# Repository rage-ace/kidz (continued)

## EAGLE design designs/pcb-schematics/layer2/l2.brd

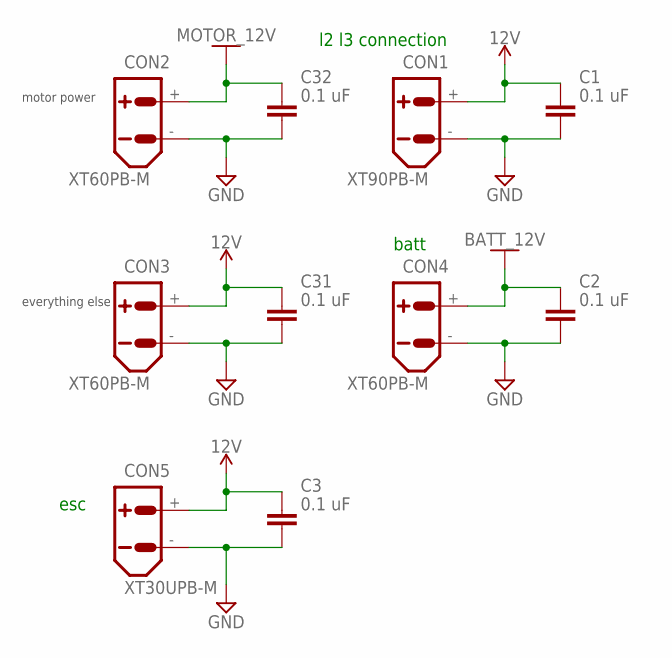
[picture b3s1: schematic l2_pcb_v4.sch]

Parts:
C1, C2, C3, C31, C32: 0.1 uF; CAPC1608X85
CON1: XT90PB-M
CON2, CON3, CON4: XT60PB-M
CON5: XT30UPB-M

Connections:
12V: C1.1, C3.1, C31.1, CON1.+, CON3.+, CON5.+
BATT_12V: C2.1, CON4.+
GND: C1.2, C2.2, C3.2, C31.2, C32.2, CON1.-, CON2.-, CON3.-, CON4.-, CON5.-
MOTOR_12V: C32.1, CON2.+

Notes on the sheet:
motor power
everything else
l2 l3 connection
batt
esc

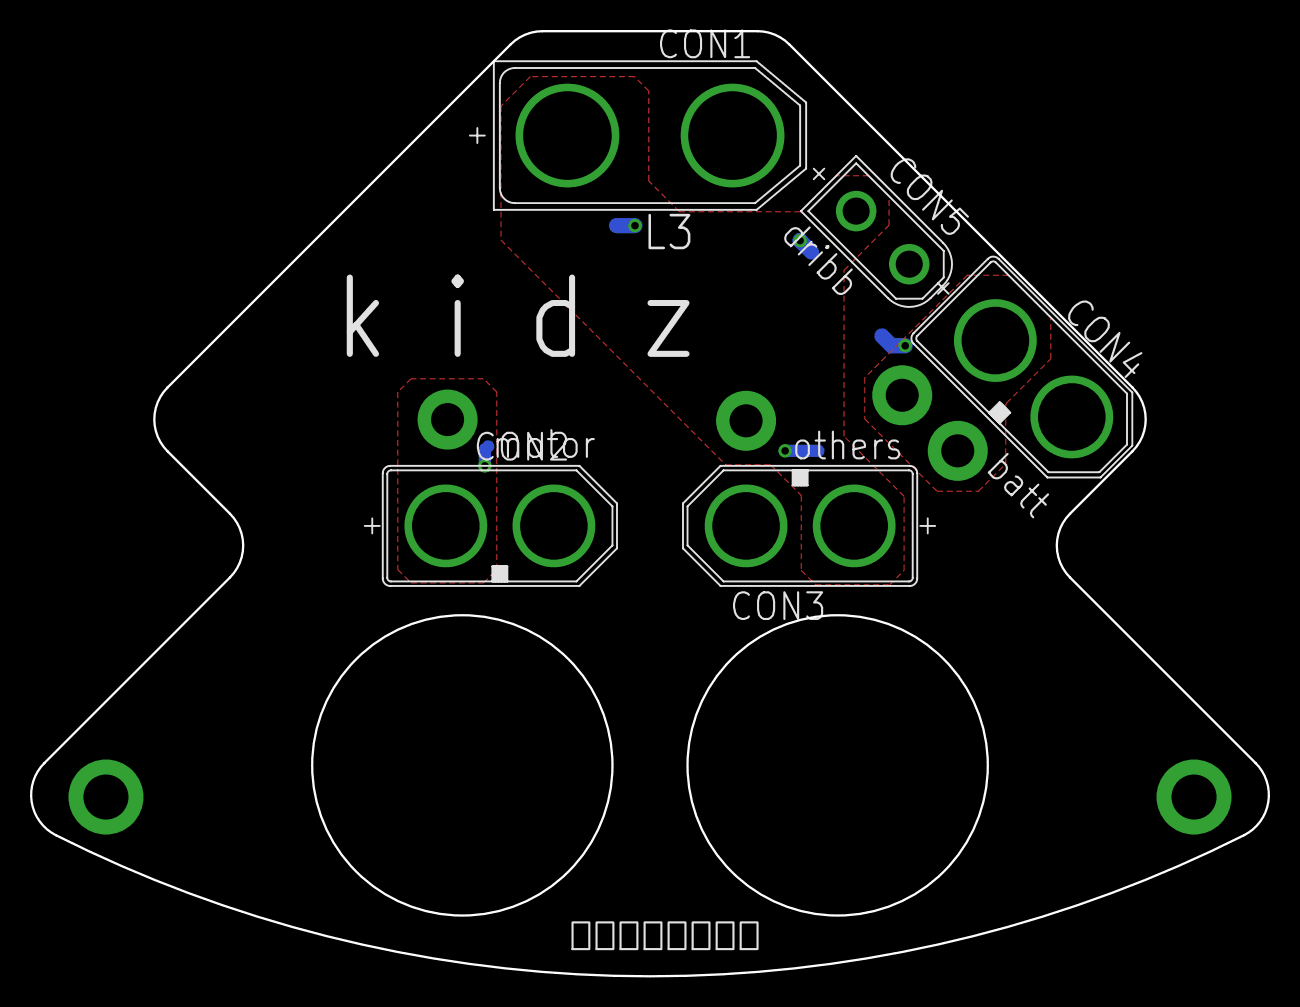
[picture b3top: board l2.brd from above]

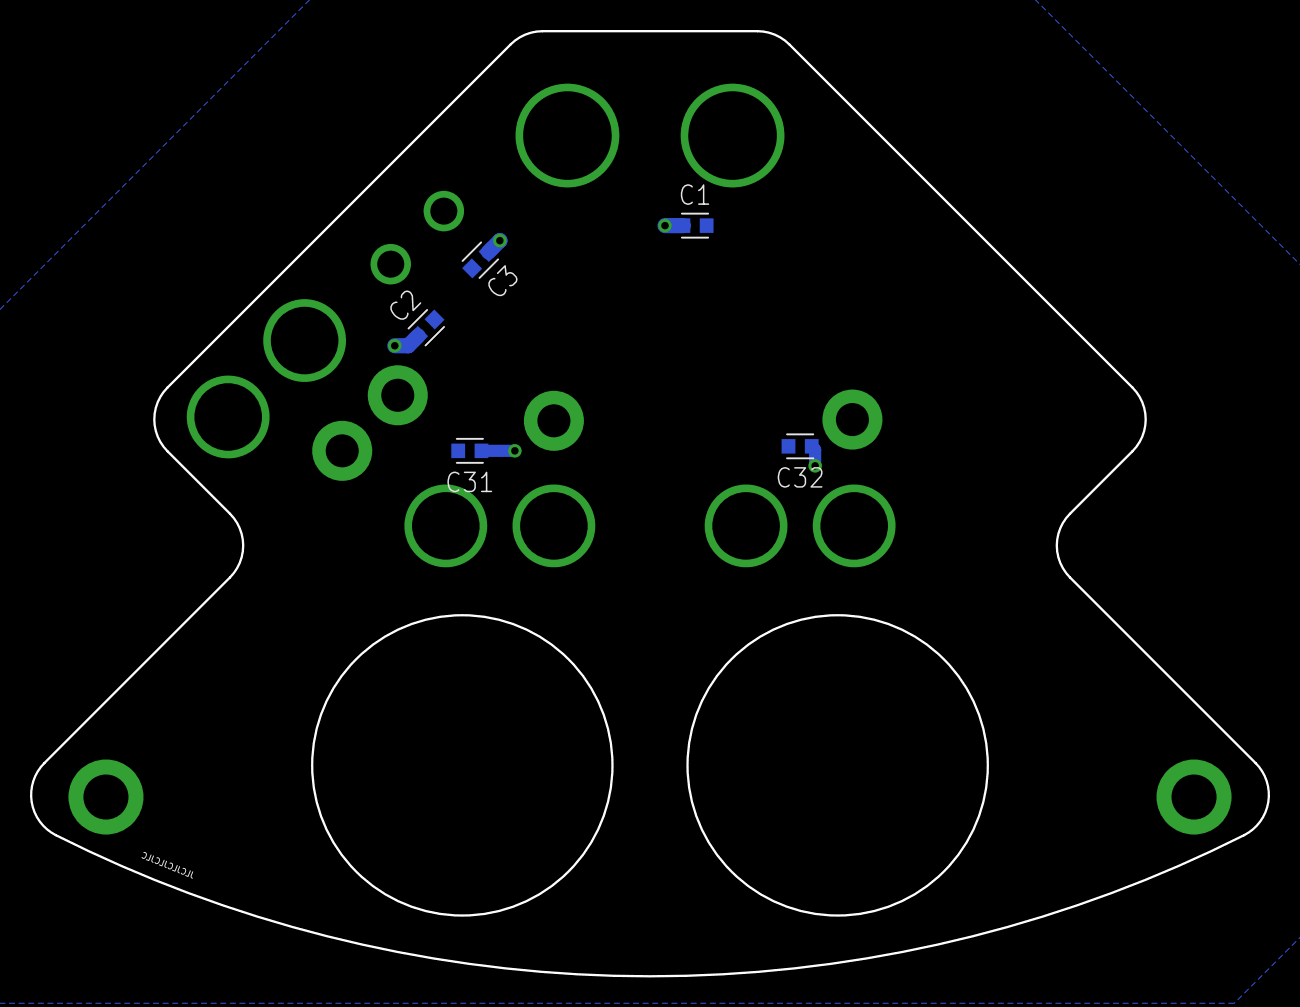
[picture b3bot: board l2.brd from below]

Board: 2 copper layers, 82.4 x 63.0 mm, 10 parts (5 on the bottom side), 4 nets.

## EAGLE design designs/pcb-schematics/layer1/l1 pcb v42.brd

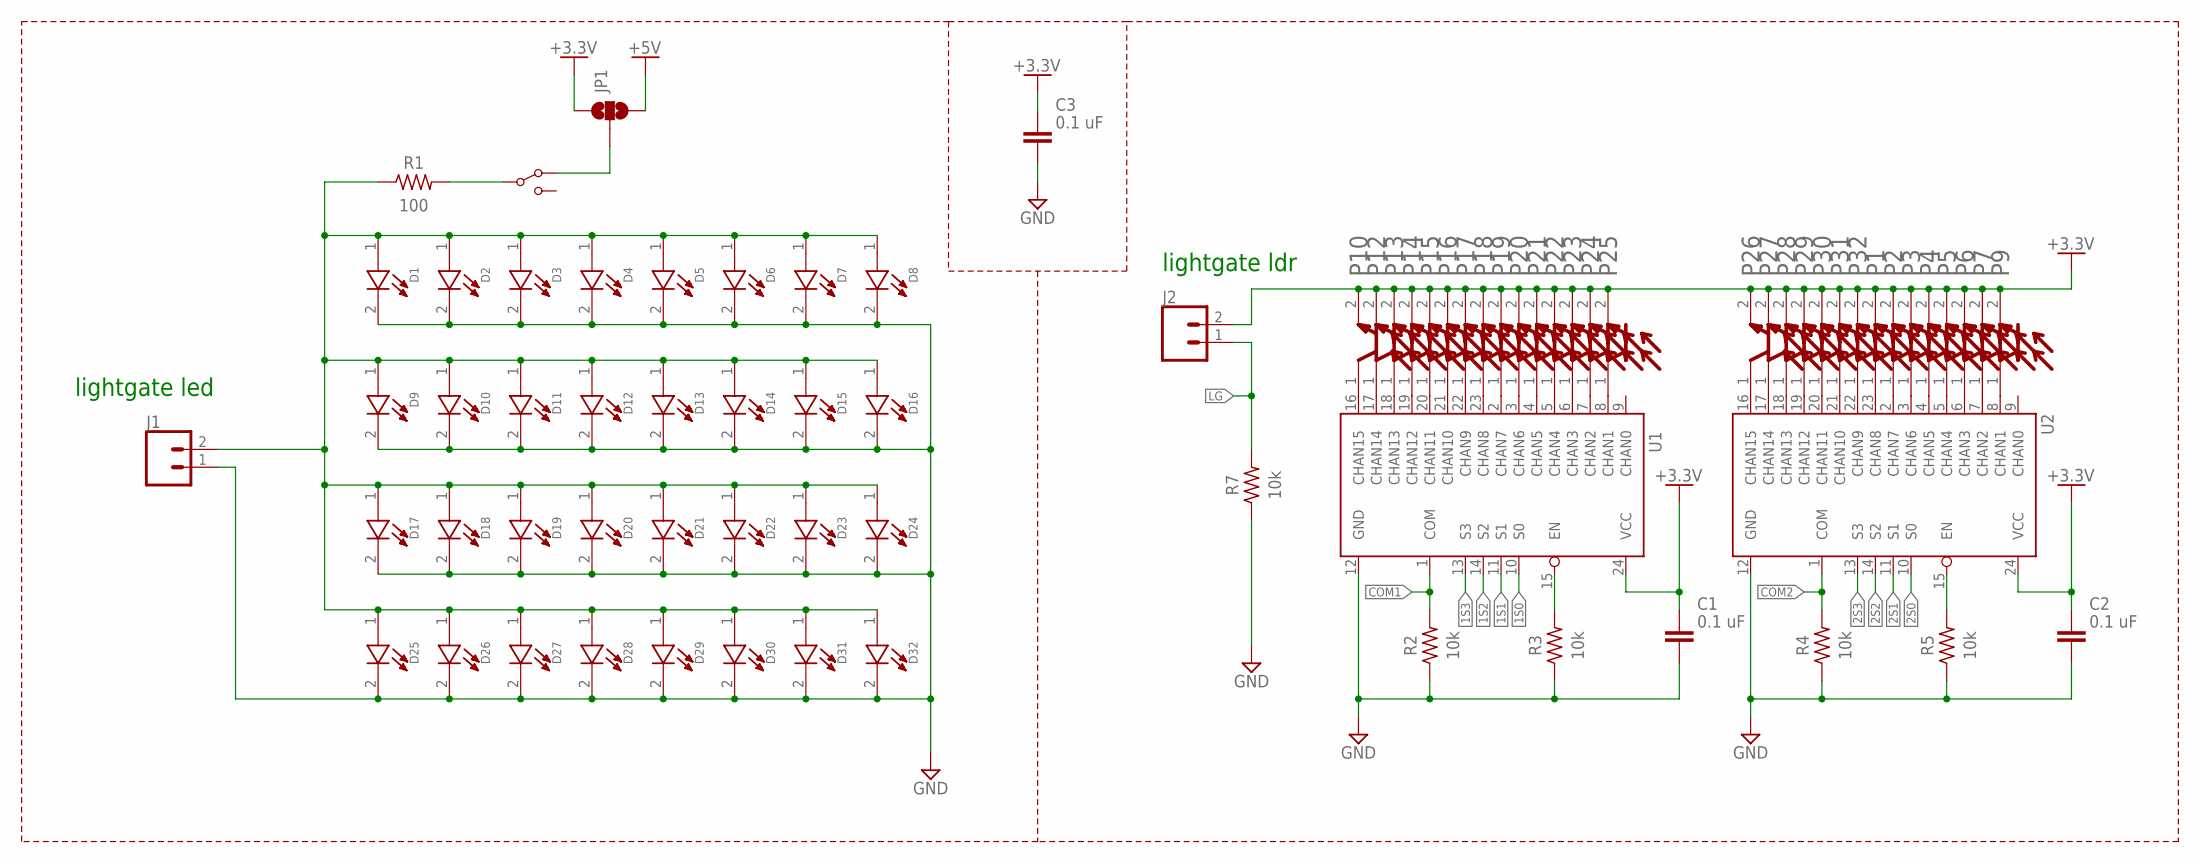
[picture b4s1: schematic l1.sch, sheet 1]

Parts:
C1, C2, C3: 0.1 uF; CAPC1608X85
D1, D2, D3, D4, D5, D6, D7, D8, D9, D10, D11, D12, D13, D14, D15, D16, D17, D18, D19, D20, D21, D22, D23, D24, D25, D26, D27, D28, D29, D30, D31, D32: OF-SMD3528WCLED; LED
J1, J2: CONN_02; 1X02
JP1: JUMPER-SMT_3_NO_SILK; SMT-JUMPER_3_NO_SILK
P1, P2, P3, P4, P5, P6, P7, P9, P10, P12, P13, P14, P15, P16, P17, P18, P19, P20, P21, P22, P23, P24, P25, P26, P27, P28, P29, P30, P31, P32: EVERLIGHT_ALS-PT19-315C-L177-TR8; ALS-PT19
R1: 100; RESC1608X60
R2, R3, R4, R5, R7: 10k; RESC1608X60
S1: SPDT-SLIDE-SWITCHSWITCH-TH; SWITCH-TH
U1, U2: 74HC4067SM96; SSOP24

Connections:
1S0: U1.10 (S0); also elsewhere on the board
1S1: U1.11 (S1); also elsewhere on the board
1S2: U1.14 (S2); also elsewhere on the board
1S3: U1.13 (S3); also elsewhere on the board
2S0: U2.10 (S0); also elsewhere on the board
2S1: U2.11 (S1); also elsewhere on the board
2S2: U2.14 (S2); also elsewhere on the board
2S3: U2.13 (S3); also elsewhere on the board
+3.3V: C1.1, C2.1, C3.1, J2.2, JP1.1, P1.2 (EMITTER), P2.2 (EMITTER), P3.2 (EMITTER), P4.2 (EMITTER), P5.2 (EMITTER), P6.2 (EMITTER), P7.2 (EMITTER), P9.2 (EMITTER), P10.2 (EMITTER), P12.2 (EMITTER), P13.2 (EMITTER), P14.2 (EMITTER), P15.2 (EMITTER), P16.2 (EMITTER), P17.2 (EMITTER), P18.2 (EMITTER), P19.2 (EMITTER), P20.2 (EMITTER), P21.2 (EMITTER), P22.2 (EMITTER), P23.2 (EMITTER), P24.2 (EMITTER), P25.2 (EMITTER), P26.2 (EMITTER), P27.2 (EMITTER), P28.2 (EMITTER), P29.2 (EMITTER), P30.2 (EMITTER), P31.2 (EMITTER), P32.2 (EMITTER), U1.24 (VCC), U2.24 (VCC); also elsewhere on the board
+5V: JP1.3; also elsewhere on the board
COM1: R2.2, U1.1 (COM); also elsewhere on the board
COM2: R4.2, U2.1 (COM); also elsewhere on the board
GND: C1.2, C2.2, C3.2, D1.2 (C), D2.2 (C), D3.2 (C), D4.2 (C), D5.2 (C), D6.2 (C), D7.2 (C), D8.2 (C), D9.2 (C), D10.2 (C), D11.2 (C), D12.2 (C), D13.2 (C), D14.2 (C), D15.2 (C), D16.2 (C), D17.2 (C), D18.2 (C), D19.2 (C), D20.2 (C), D21.2 (C), D22.2 (C), D23.2 (C), D24.2 (C), D25.2 (C), D26.2 (C), D27.2 (C), D28.2 (C), D29.2 (C), D30.2 (C), D31.2 (C), D32.2 (C), J1.1, R2.1, R3.1, R4.1, R5.1, R7.1, U1.12 (GND), U2.12 (GND); also elsewhere on the board
LG: J2.1, R7.2; also elsewhere on the board
unnamed: JP1.2, S1.P$1
unnamed: R3.2, U1.15 (EN)
unnamed: D1.1 (A), D2.1 (A), D3.1 (A), D4.1 (A), D5.1 (A), D6.1 (A), D7.1 (A), D8.1 (A), D9.1 (A), D10.1 (A), D11.1 (A), D12.1 (A), D13.1 (A), D14.1 (A), D15.1 (A), D16.1 (A), D17.1 (A), D18.1 (A), D19.1 (A), D20.1 (A), D21.1 (A), D22.1 (A), D23.1 (A), D24.1 (A), D25.1 (A), D26.1 (A), D27.1 (A), D28.1 (A), D29.1 (A), D30.1 (A), D31.1 (A), D32.1 (A), J1.2, R1.1
unnamed: R5.2, U2.15 (EN)
unnamed: R1.2, S1.P$2
unnamed: P25.1 (COLLECTOR), U1.8 (CHAN1)
unnamed: P17.1 (COLLECTOR), U1.22 (CHAN9)
unnamed: P18.1 (COLLECTOR), U1.23 (CHAN8)
unnamed: P19.1 (COLLECTOR), U1.2 (CHAN7)
unnamed: P20.1 (COLLECTOR), U1.3 (CHAN6)
unnamed: P21.1 (COLLECTOR), U1.4 (CHAN5)
unnamed: P22.1 (COLLECTOR), U1.5 (CHAN4)
unnamed: P23.1 (COLLECTOR), U1.6 (CHAN3)
unnamed: P24.1 (COLLECTOR), U1.7 (CHAN2)
unnamed: P10.1 (COLLECTOR), U1.16 (CHAN15)
unnamed: P12.1 (COLLECTOR), U1.17 (CHAN14)
unnamed: P13.1 (COLLECTOR), U1.18 (CHAN13)
unnamed: P14.1 (COLLECTOR), U1.19 (CHAN12)
unnamed: P15.1 (COLLECTOR), U1.20 (CHAN11)
unnamed: P16.1 (COLLECTOR), U1.21 (CHAN10)
unnamed: P9.1 (COLLECTOR), U2.8 (CHAN1)
unnamed: P1.1 (COLLECTOR), U2.23 (CHAN8)
unnamed: P2.1 (COLLECTOR), U2.2 (CHAN7)
unnamed: P3.1 (COLLECTOR), U2.3 (CHAN6)
unnamed: P4.1 (COLLECTOR), U2.4 (CHAN5)
unnamed: P5.1 (COLLECTOR), U2.5 (CHAN4)
unnamed: P6.1 (COLLECTOR), U2.6 (CHAN3)
unnamed: P7.1 (COLLECTOR), U2.7 (CHAN2)
unnamed: P26.1 (COLLECTOR), U2.16 (CHAN15)
unnamed: P27.1 (COLLECTOR), U2.17 (CHAN14)
unnamed: P28.1 (COLLECTOR), U2.18 (CHAN13)
unnamed: P29.1 (COLLECTOR), U2.19 (CHAN12)
unnamed: P30.1 (COLLECTOR), U2.20 (CHAN11)
unnamed: P31.1 (COLLECTOR), U2.21 (CHAN10)
unnamed: P32.1 (COLLECTOR), U2.22 (CHAN9)

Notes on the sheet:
lightgate led
lightgate ldr

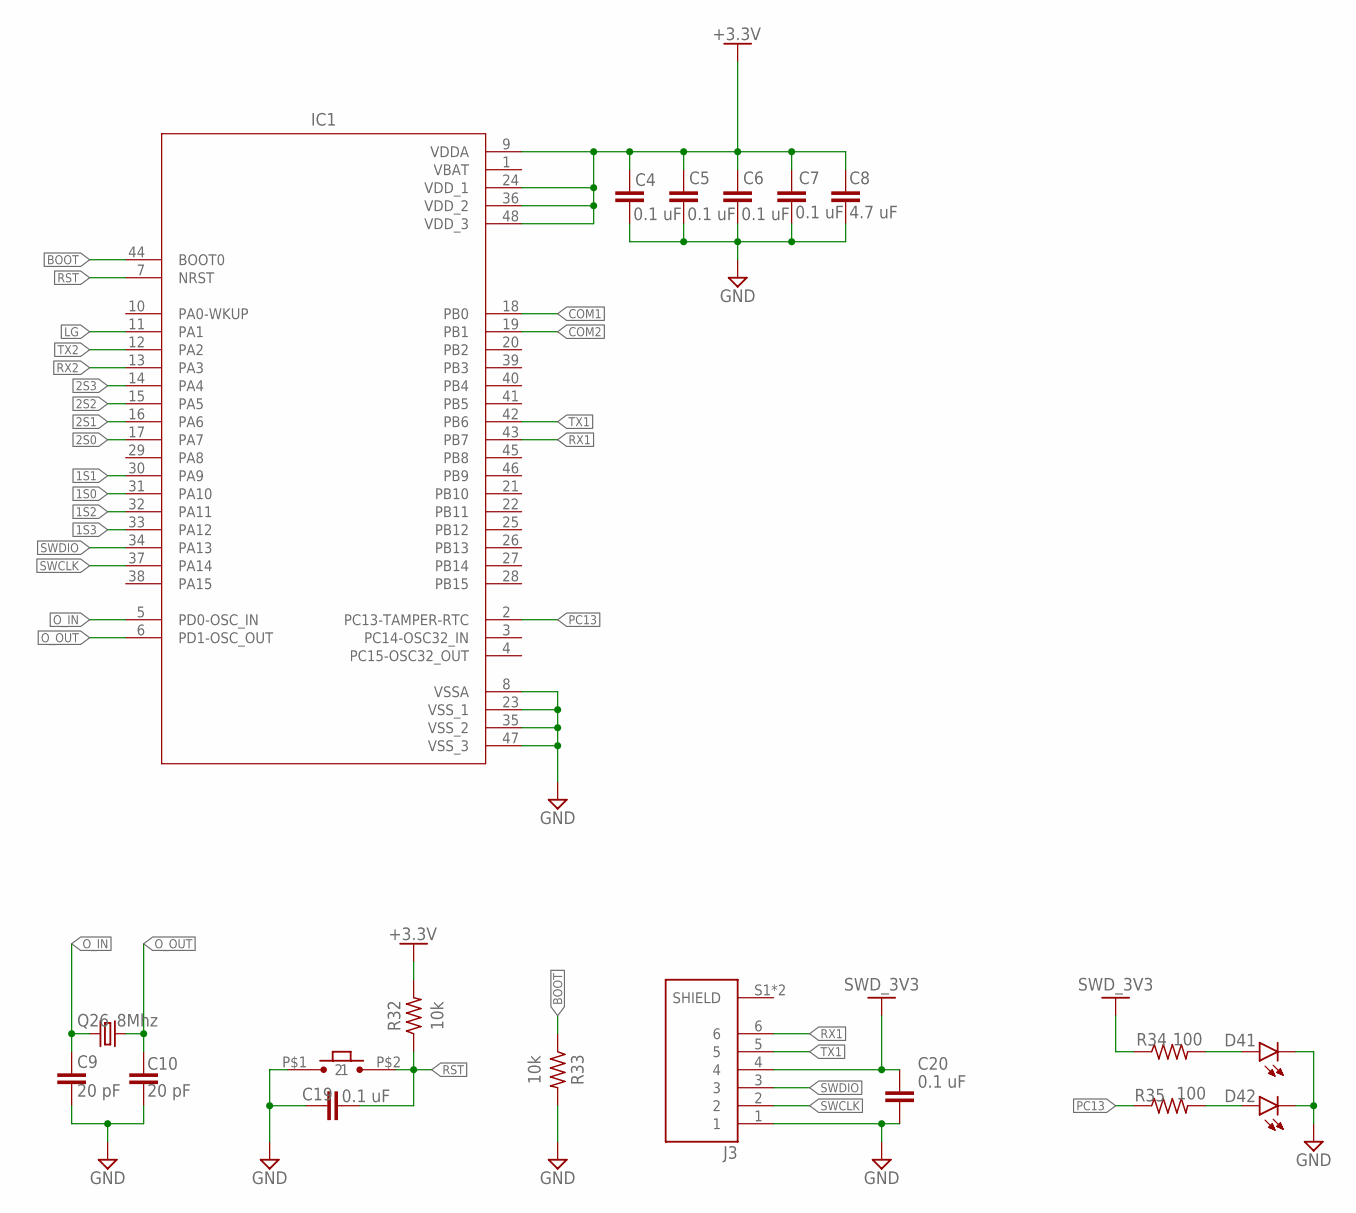
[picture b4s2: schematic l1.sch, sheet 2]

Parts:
C4, C5, C6, C7, C19, C20: 0.1 uF; CAPC1608X85
C8: 4.7 uF; CAPC1608X85
C9, C10: 20 pF; CAPC1608X85
D41, D42: CHIP-FLAT-G_0603-0.35MM; LEDC1608X35N_FLAT-G
IC1: STM32F103_QFP; QFP50P900X900X160-48N
J3: SM06B-SRSS-TB(LF)(SN); JST_SM06B-SRSS-TB(LF)(SN)
Q26: 8Mhz; CTS406
R32, R33: 10k; RESC1608X60
R34, R35: 100; RESC1608X60
U$1: SMOL_TACTILE_3X4MM

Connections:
1S0: IC1.31 (PA10); also elsewhere on the board
1S1: IC1.30 (PA9); also elsewhere on the board
1S2: IC1.32 (PA11); also elsewhere on the board
1S3: IC1.33 (PA12); also elsewhere on the board
2S0: IC1.17 (PA7); also elsewhere on the board
2S1: IC1.16 (PA6); also elsewhere on the board
2S2: IC1.15 (PA5); also elsewhere on the board
2S3: IC1.14 (PA4); also elsewhere on the board
+3.3V: C4.1, C5.1, C6.1, C7.1, C8.1, IC1.9 (VDDA), IC1.24 (VDD_1), IC1.36 (VDD_2), IC1.48 (VDD_3), R32.2; also elsewhere on the board
BOOT: IC1.44 (BOOT0), R33.1
COM1: IC1.18 (PB0); also elsewhere on the board
COM2: IC1.19 (PB1); also elsewhere on the board
GND: C4.2, C5.2, C6.2, C7.2, C8.2, C9.2, C10.2, C19.1, C20.2, D41.C, D42.C, IC1.8 (VSSA), IC1.23 (VSS_1), IC1.35 (VSS_2), IC1.47 (VSS_3), J3.1, R33.2, U$1.P$1 (1); also elsewhere on the board
LG: IC1.11 (PA1); also elsewhere on the board
unnamed: D41.A, R34.2
unnamed: D42.A, R35.2
O_IN: C9.1, IC1.5 (PD0-OSC_IN), Q26.1
O_OUT: C10.1, IC1.6 (PD1-OSC_OUT), Q26.3 (2)
PC13: IC1.2 (PC13-TAMPER-RTC), R35.1
RST: C19.2, IC1.7 (NRST), R32.1, U$1.P$2 (2)
RX1: IC1.43 (PB7), J3.6
RX2: IC1.13 (PA3); also elsewhere on the board
SWCLK: IC1.37 (PA14), J3.2
SWDIO: IC1.34 (PA13), J3.3
SWD_3V3: C20.1, J3.4, R34.1
TX1: IC1.42 (PB6), J3.5
TX2: IC1.12 (PA2); also elsewhere on the board
VBAT: IC1.1 (VBAT)

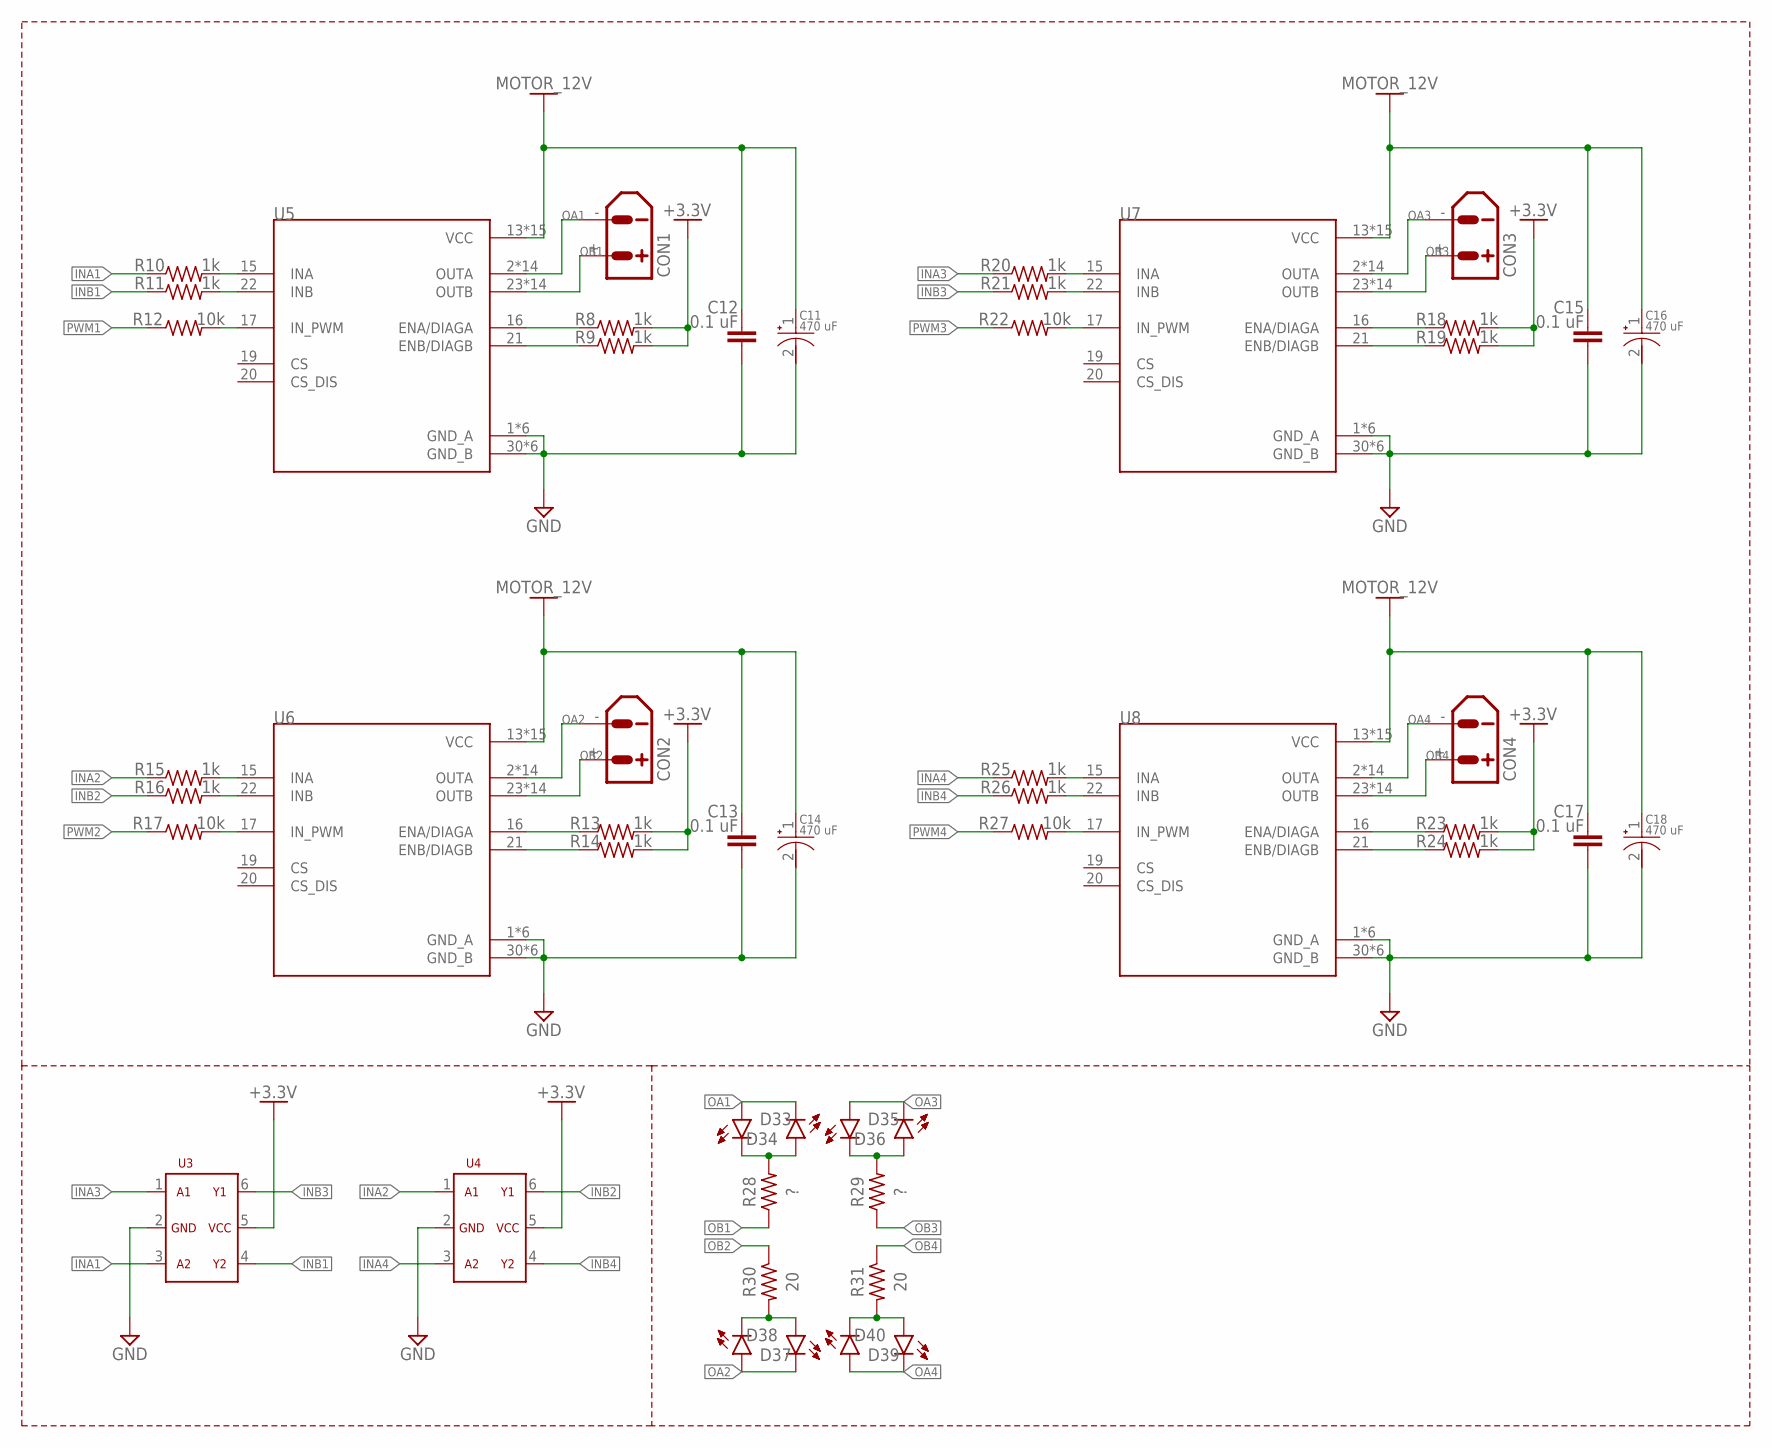
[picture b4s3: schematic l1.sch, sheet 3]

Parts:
C11, C14, C16, C18: 470 uF; 6.3_X_7.7
C12, C13, C15, C17: 0.1 uF; CAPC1608X85
CON1, CON2, CON3, CON4: XT30UPB-M
D33, D34, D35, D36, D37, D38, D39, D40: CHIP-FLAT-G_0603-0.35MM; LEDC1608X35N_FLAT-G
R8, R9, R10, R11, R13, R14, R15, R16, R18, R19, R20, R21, R23, R24, R25, R26: 1k; RESC1608X60
R12, R17, R22, R27: 10k; RESC1608X60
R28, R29: ?; RESC1608X60
R30, R31: 20; RESC1608X60
U3, U4: SN74LVC2G04DBVR; SOT23-6
U5, U6, U7, U8: VNH5050A-E; SOP50P1030X247-39N

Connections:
+3.3V: R8.2, R9.2, R13.2, R14.2, R18.2, R19.2, R23.2, R24.2, U3.5, U4.5; also elsewhere on the board
GND: C11.2, C12.2, C13.2, C14.2, C15.2, C16.2, C17.2, C18.2, U3.2, U4.2, U5.1 (GND_A), U5.3 (GND_A), U5.4 (GND_A), U5.5 (GND_A), U5.6 (GND_A), U5.7 (GND_A), U5.30 (GND_B), U5.31 (GND_B), U5.32 (GND_B), U5.33 (GND_B), U5.34 (GND_B), U5.36 (GND_B), U6.1 (GND_A), U6.3 (GND_A), U6.4 (GND_A), U6.5 (GND_A), U6.6 (GND_A), U6.7 (GND_A), U6.30 (GND_B), U6.31 (GND_B), U6.32 (GND_B), U6.33 (GND_B), U6.34 (GND_B), U6.36 (GND_B), U7.1 (GND_A), U7.3 (GND_A), U7.4 (GND_A), U7.5 (GND_A), U7.6 (GND_A), U7.7 (GND_A), U7.30 (GND_B), U7.31 (GND_B), U7.32 (GND_B), U7.33 (GND_B), U7.34 (GND_B), U7.36 (GND_B), U8.1 (GND_A), U8.3 (GND_A), U8.4 (GND_A), U8.5 (GND_A), U8.6 (GND_A), U8.7 (GND_A), U8.30 (GND_B), U8.31 (GND_B), U8.32 (GND_B), U8.33 (GND_B), U8.34 (GND_B), U8.36 (GND_B); also elsewhere on the board
INA1: R10.1, U3.3; also elsewhere on the board
INA2: R15.1, U4.1; also elsewhere on the board
INA3: R20.1, U3.1; also elsewhere on the board
INA4: R25.1, U4.3; also elsewhere on the board
INB1: R11.1, U3.4
INB2: R16.1, U4.6
INB3: R21.1, U3.6
INB4: R26.1, U4.4
MOTOR_12V: C11.1, C12.1, C13.1, C14.1, C15.1, C16.1, C17.1, C18.1, U5.13 (VCC), U5.24 (VCC), U5.39 (VCC), U5.39_1 (VCC), U5.39_2 (VCC), U5.39_3 (VCC), U5.39_4 (VCC), U5.39_5 (VCC), U5.39_6 (VCC), U5.39_7 (VCC), U5.39_8 (VCC), U5.39_9 (VCC), U5.39_10 (VCC), U5.39_11 (VCC), U5.39_12 (VCC), U6.13 (VCC), U6.24 (VCC), U6.39 (VCC), U6.39_1 (VCC), U6.39_2 (VCC), U6.39_3 (VCC), U6.39_4 (VCC), U6.39_5 (VCC), U6.39_6 (VCC), U6.39_7 (VCC), U6.39_8 (VCC), U6.39_9 (VCC), U6.39_10 (VCC), U6.39_11 (VCC), U6.39_12 (VCC), U7.13 (VCC), U7.24 (VCC), U7.39 (VCC), U7.39_1 (VCC), U7.39_2 (VCC), U7.39_3 (VCC), U7.39_4 (VCC), U7.39_5 (VCC), U7.39_6 (VCC), U7.39_7 (VCC), U7.39_8 (VCC), U7.39_9 (VCC), U7.39_10 (VCC), U7.39_11 (VCC), U7.39_12 (VCC), U8.13 (VCC), U8.24 (VCC), U8.39 (VCC), U8.39_1 (VCC), U8.39_2 (VCC), U8.39_3 (VCC), U8.39_4 (VCC), U8.39_5 (VCC), U8.39_6 (VCC), U8.39_7 (VCC), U8.39_8 (VCC), U8.39_9 (VCC), U8.39_10 (VCC), U8.39_11 (VCC), U8.39_12 (VCC); also elsewhere on the board
unnamed: R10.2, U5.15 (INA)
unnamed: R11.2, U5.22 (INB)
unnamed: R12.2, U5.17 (IN_PWM)
unnamed: R8.1, U5.16 (ENA/DIAGA)
unnamed: R9.1, U5.21 (ENB/DIAGB)
unnamed: D35.C, D36.A, R29.2
unnamed: D33.C, D34.A, R28.2
unnamed: R15.2, U6.15 (INA)
unnamed: R16.2, U6.22 (INB)
unnamed: R17.2, U6.17 (IN_PWM)
unnamed: R13.1, U6.16 (ENA/DIAGA)
unnamed: R14.1, U6.21 (ENB/DIAGB)
unnamed: D37.C, D38.A, R30.2
unnamed: R20.2, U7.15 (INA)
unnamed: R21.2, U7.22 (INB)
unnamed: R22.2, U7.17 (IN_PWM)
unnamed: R18.1, U7.16 (ENA/DIAGA)
unnamed: R19.1, U7.21 (ENB/DIAGB)
unnamed: D39.C, D40.A, R31.2
unnamed: R25.2, U8.15 (INA)
unnamed: R26.2, U8.22 (INB)
unnamed: R27.2, U8.17 (IN_PWM)
unnamed: R23.1, U8.16 (ENA/DIAGA)
unnamed: R24.1, U8.21 (ENB/DIAGB)
OA1: CON1.-, D33.A, D34.C, U5.2 (OUTA), U5.8 (OUTA), U5.9 (OUTA), U5.10 (OUTA), U5.11 (OUTA), U5.12 (OUTA), U5.14 (OUTA), U5.38 (OUTA), U5.38_1 (OUTA), U5.38_2 (OUTA), U5.38_3 (OUTA), U5.38_4 (OUTA), U5.38_5 (OUTA), U5.38_6 (OUTA)
OA2: CON2.-, D37.A, D38.C, U6.2 (OUTA), U6.8 (OUTA), U6.9 (OUTA), U6.10 (OUTA), U6.11 (OUTA), U6.12 (OUTA), U6.14 (OUTA), U6.38 (OUTA), U6.38_1 (OUTA), U6.38_2 (OUTA), U6.38_3 (OUTA), U6.38_4 (OUTA), U6.38_5 (OUTA), U6.38_6 (OUTA)
OA3: CON3.-, D35.A, D36.C, U7.2 (OUTA), U7.8 (OUTA), U7.9 (OUTA), U7.10 (OUTA), U7.11 (OUTA), U7.12 (OUTA), U7.14 (OUTA), U7.38 (OUTA), U7.38_1 (OUTA), U7.38_2 (OUTA), U7.38_3 (OUTA), U7.38_4 (OUTA), U7.38_5 (OUTA), U7.38_6 (OUTA)
OA4: CON4.-, D39.A, D40.C, U8.2 (OUTA), U8.8 (OUTA), U8.9 (OUTA), U8.10 (OUTA), U8.11 (OUTA), U8.12 (OUTA), U8.14 (OUTA), U8.38 (OUTA), U8.38_1 (OUTA), U8.38_2 (OUTA), U8.38_3 (OUTA), U8.38_4 (OUTA), U8.38_5 (OUTA), U8.38_6 (OUTA)
OB1: CON1.+, R28.1, U5.23 (OUTB), U5.25 (OUTB), U5.26 (OUTB), U5.27 (OUTB), U5.28 (OUTB), U5.29 (OUTB), U5.35 (OUTB), U5.37 (OUTB), U5.37_1 (OUTB), U5.37_2 (OUTB), U5.37_3 (OUTB), U5.37_4 (OUTB), U5.37_5 (OUTB), U5.37_6 (OUTB)
OB2: CON2.+, R30.1, U6.23 (OUTB), U6.25 (OUTB), U6.26 (OUTB), U6.27 (OUTB), U6.28 (OUTB), U6.29 (OUTB), U6.35 (OUTB), U6.37 (OUTB), U6.37_1 (OUTB), U6.37_2 (OUTB), U6.37_3 (OUTB), U6.37_4 (OUTB), U6.37_5 (OUTB), U6.37_6 (OUTB)
OB3: CON3.+, R29.1, U7.23 (OUTB), U7.25 (OUTB), U7.26 (OUTB), U7.27 (OUTB), U7.28 (OUTB), U7.29 (OUTB), U7.35 (OUTB), U7.37 (OUTB), U7.37_1 (OUTB), U7.37_2 (OUTB), U7.37_3 (OUTB), U7.37_4 (OUTB), U7.37_5 (OUTB), U7.37_6 (OUTB)
OB4: CON4.+, R31.1, U8.23 (OUTB), U8.25 (OUTB), U8.26 (OUTB), U8.27 (OUTB), U8.28 (OUTB), U8.29 (OUTB), U8.35 (OUTB), U8.37 (OUTB), U8.37_1 (OUTB), U8.37_2 (OUTB), U8.37_3 (OUTB), U8.37_4 (OUTB), U8.37_5 (OUTB), U8.37_6 (OUTB)
PWM1: R12.1; also elsewhere on the board
PWM2: R17.1; also elsewhere on the board
PWM3: R22.1; also elsewhere on the board
PWM4: R27.1; also elsewhere on the board

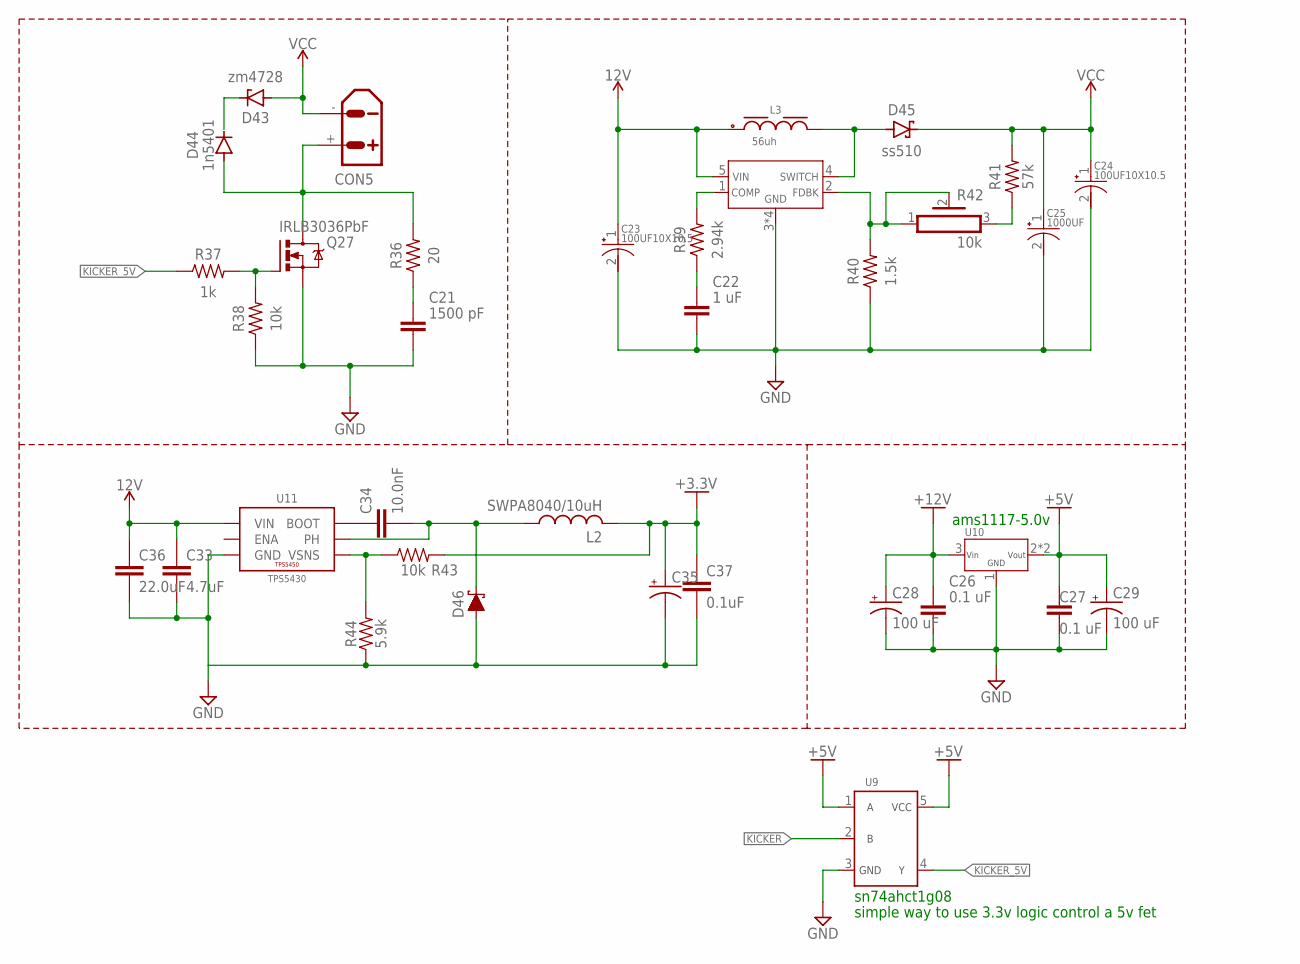
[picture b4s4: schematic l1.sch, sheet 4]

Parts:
C21: 1500 pF; CAPC1608X85
C22: 1 uF; CAPC1608X85
C23, C24: 100UF10X10.5; 10_X_10.5
C25: 1000UF; 16_X_25
C26, C27: 0.1 uF; CAPC1608X85
C28, C29: 100 uF; CAPMP7343X310N
C33: 4.7uF; C0603
C34: 10.0nF; C0603
C35: 220uF; D/7343-31R
C36: 22.0uF; C1210
C37: 0.1uF; C0603
CON5: XT30UPB-F
D43: zm4728; DIOMELF5024
D44: 1n5401; DO-201AD
D45: ss510; DIOM5226X290N
D46: 3A/40V/500mV; SMA-DIODE
L2: SWPA8040/10uH; SWPA8040
L3: 56uh; WE-PD_7345R
Q27: IRLB3036PbF; TO220BV
R36: 20; RESAD724W46L381D178B
R37: 1k; RESC1608X60
R38: 10k; RESC1608X60
R39: 2.94k; RESC1608X60
R40: 1.5k; RESC1608X60
R41: 57k; RESC1608X60
R42: 10k; PV36X
R43: 10k; R0603
R44: 5.9k; R0603
U9: SN74AHCT1G08; SOT23-5
U10: AMS1117-5.0; SOT223
U11: TPS5430; POWERPAD-SOIC-8
U$5: LM2587; TO263-5

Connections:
12V: C23.1, C33.1, C36.1, L3.1, U11.7 (VIN), U$5.5; also elsewhere on the board
+3.3V: C35.+, C37.1, L2.P2 (2), R43.2; also elsewhere on the board
+5V: C27.1, C29.1 (+), U9.1, U9.5, U10.2, U10.4; also elsewhere on the board
+12V: C26.1, C28.1 (+), U10.3
GND: C21.2, C22.2, C23.2, C24.2, C25.2, C26.2, C27.2, C28.2 (-), C29.2 (-), C33.2, C35.-, C36.2, C37.2, D46.A, Q27.S, R38.1, R40.1, R44.1, U9.3, U10.1, U11.6 (GND), U11.9 (GND), U11.P$1 (GND), U11.P$2 (GND), U11.P$3 (GND), U11.P$4 (GND), U11.P$5 (GND), U11.P$6 (GND), U$5.3, U$5.6, U$5.P$1, U$5.P$2; also elsewhere on the board
KICKER: U9.2; also elsewhere on the board
KICKER_5V: R37.1, U9.4
unnamed: C34.2, D46.C, L2.P1 (1), U11.8 (PH)
unnamed: CON5.+, D44.A, Q27.D, R36.2
unnamed: C21.1, R36.1
unnamed: D43.1 (C), D44.C
unnamed: Q27.G, R37.2, R38.2
unnamed: D45.1 (A), L3.2, U$5.4
unnamed: R39.2, U$5.1
unnamed: C22.1, R39.1
unnamed: R41.1, R42.3
unnamed: R40.2, R42.1, R42.2, U$5.2
unnamed: R43.1, R44.2, U11.4 (VSNS)
unnamed: C34.1, U11.1 (BOOT)
VCC: C24.1, C25.1, CON5.-, D43.2 (A), D45.2 (C), R41.2; also elsewhere on the board

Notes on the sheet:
sn74ahct1g08
simple way to use 3.3v logic control a 5v fet
ams1117-5.0v

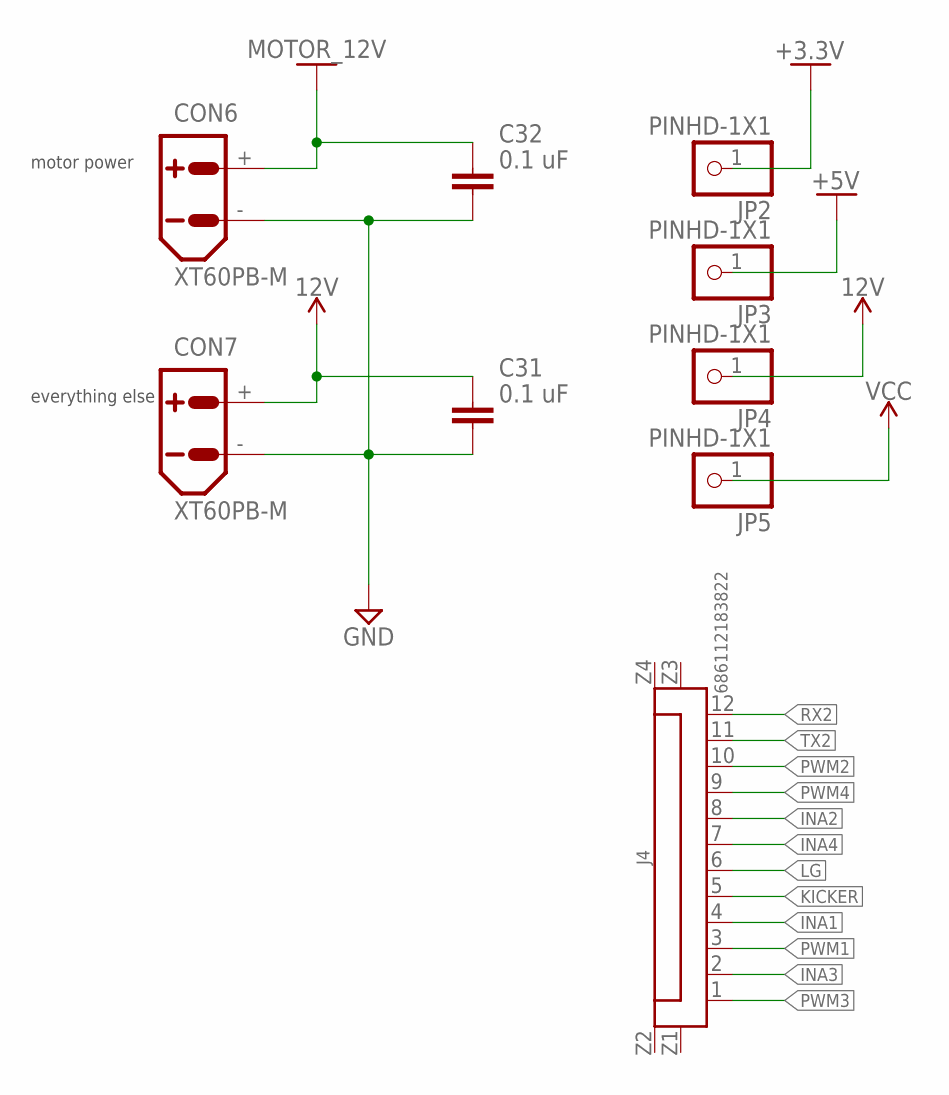
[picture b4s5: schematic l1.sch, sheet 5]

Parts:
C31, C32: 0.1 uF; CAPC1608X85
CON6, CON7: XT60PB-M
J4: 686112183822
JP2, JP3, JP4, JP5: PINHD-1X1; 1X01

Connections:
12V: C31.1, CON7.+, JP4.1; also elsewhere on the board
+3.3V: JP2.1; also elsewhere on the board
+5V: JP3.1; also elsewhere on the board
GND: C31.2, C32.2, CON6.-, CON7.-; also elsewhere on the board
INA1: J4.4; also elsewhere on the board
INA2: J4.8; also elsewhere on the board
INA3: J4.2; also elsewhere on the board
INA4: J4.7; also elsewhere on the board
KICKER: J4.5; also elsewhere on the board
LG: J4.6; also elsewhere on the board
MOTOR_12V: C32.1, CON6.+; also elsewhere on the board
PWM1: J4.3; also elsewhere on the board
PWM2: J4.10; also elsewhere on the board
PWM3: J4.1; also elsewhere on the board
PWM4: J4.9; also elsewhere on the board
RX2: J4.12; also elsewhere on the board
TX2: J4.11; also elsewhere on the board
VCC: JP5.1; also elsewhere on the board

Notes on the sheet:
motor power
everything else
